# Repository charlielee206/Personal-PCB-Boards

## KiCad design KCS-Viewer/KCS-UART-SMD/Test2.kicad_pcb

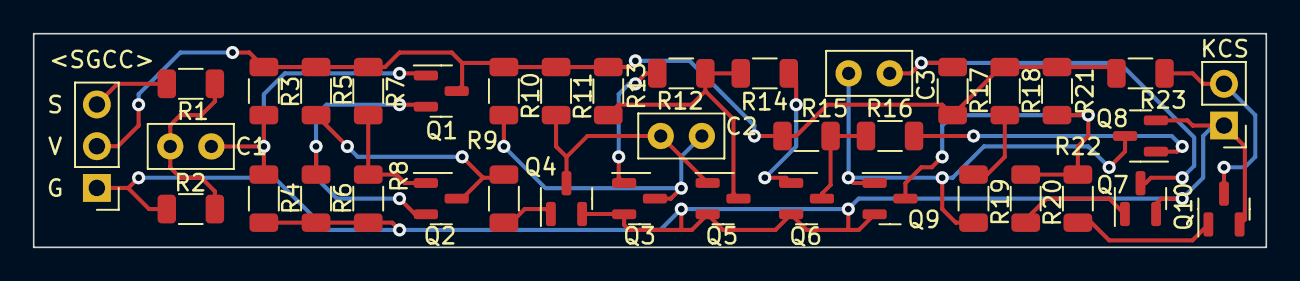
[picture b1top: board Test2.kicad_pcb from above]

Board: 2 copper layers, 75.0 x 13.0 mm, 38 parts (0 on the bottom side), 23 nets.

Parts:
C1, C2, C3: 100n; C_Disc_D5.0mm_W2.5mm_P2.50mm
G: Screw_Terminal_01x03; PinHeader_1x03_P2.54mm_Vertical
KCS: Screw_Terminal_01x02; PinHeader_1x02_P2.54mm_Vertical
Q1, Q2, Q3, Q4, Q5, Q6, Q7, Q8, Q9, Q10: MMBT3904; SOT-23
R1: 150R; R_1206_3216Metric
R2: 75R; R_1206_3216Metric
R3, R7, R9, R12, R14, R16, R20, R22: 10K; R_1206_3216Metric
R4, R8: 3K; R_1206_3216Metric
R5, R10, R13, R15, R17, R21, R23: 2R2K; R_1206_3216Metric
R6: 100R; R_1206_3216Metric
R11: 22K; R_1206_3216Metric
R18: 12K; R_1206_3216Metric
R19: 68K; R_1206_3216Metric

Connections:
GND: G.1, KCS.1, Q3.2 (E), Q4.2 (E), Q5.2 (E), Q6.2 (E), Q7.2 (E), Q8.2 (E), Q9.2 (E), Q10.2 (E), R2.2, R4.2, R6.2, R8.2
unnamed: C1.1, R1.2, R2.1
unnamed: KCS.2, Q10.3 (C), R23.2
unnamed: C1.2, Q1.1 (B), R3.2, R4.1
unnamed: Q1.2 (E), Q2.2 (E), R6.1
unnamed: G.3, R1.1
unnamed: Q2.3 (C), R5.2, R9.1
unnamed: G.2, Q1.3 (C), R3.1, R5.1, R7.1, R10.1, R11.1, R13.1, R15.1, R17.1, R18.1, R21.1, R23.1
unnamed: Q2.1 (B), R7.2, R8.1
unnamed: Q4.1 (B), R9.2
unnamed: C2.1, Q3.3 (C), R10.2
unnamed: C2.2, Q4.3 (C), Q5.1 (B), R11.2
unnamed: Q3.1 (B), R12.1
unnamed: Q5.3 (C), R12.2, R13.2, R14.1
unnamed: Q6.1 (B), R14.2
unnamed: Q6.3 (C), R15.2, R16.1
unnamed: Q8.1 (B), R16.2
unnamed: C3.1, Q7.3 (C), R17.2
unnamed: R18.2, R19.1
unnamed: C3.2, Q8.3 (C), Q9.1 (B), R19.2
unnamed: Q7.1 (B), R20.1
unnamed: Q9.3 (C), R20.2, R21.2, R22.1
unnamed: Q10.1 (B), R22.2

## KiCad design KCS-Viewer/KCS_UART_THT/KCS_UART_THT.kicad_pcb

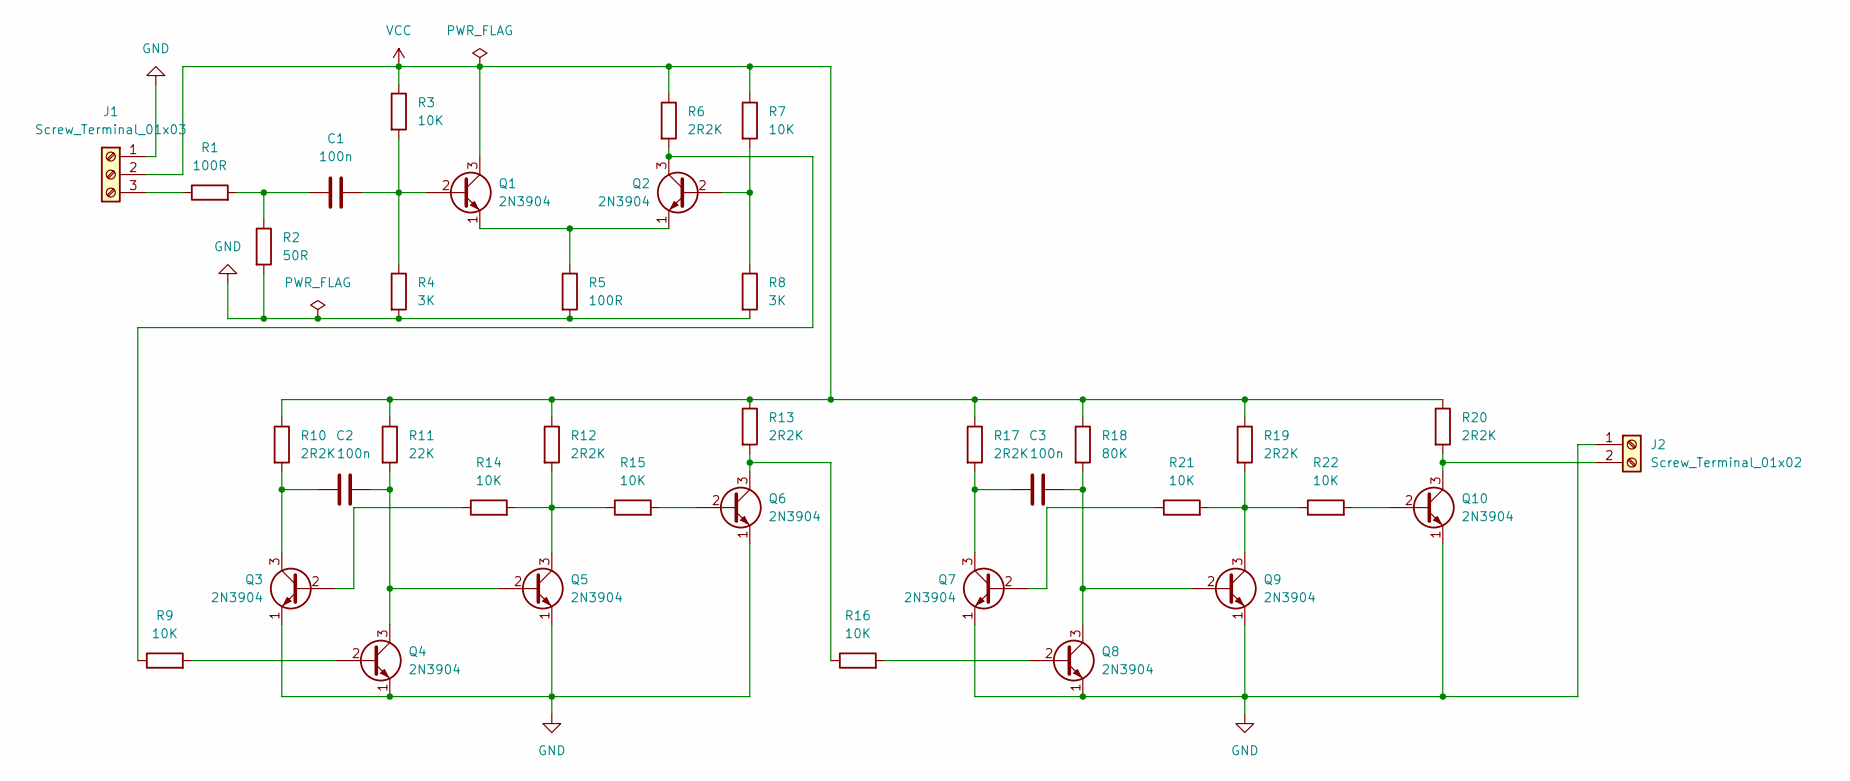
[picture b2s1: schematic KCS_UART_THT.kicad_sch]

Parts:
C1, C2, C3: 100n; C_Disc_D5.0mm_W2.5mm_P2.50mm
J1: Screw_Terminal_01x03; PinHeader_1x03_P2.54mm_Vertical
J2: Screw_Terminal_01x02; PinHeader_1x02_P2.54mm_Vertical
Q1, Q2, Q3, Q4, Q5, Q6, Q7, Q8, Q9, Q10: 2N3904; TO-92_Inline
R1, R5: 100R; R_Axial_DIN0207_L6.3mm_D2.5mm_P10.16mm_Horizontal
R2: 50R; R_Axial_DIN0207_L6.3mm_D2.5mm_P10.16mm_Horizontal
R3, R7, R9, R14, R15, R16, R21, R22: 10K; R_Axial_DIN0207_L6.3mm_D2.5mm_P10.16mm_Horizontal
R4, R8: 3K; R_Axial_DIN0207_L6.3mm_D2.5mm_P10.16mm_Horizontal
R6, R10, R12, R13, R17, R19, R20: 2R2K; R_Axial_DIN0207_L6.3mm_D2.5mm_P10.16mm_Horizontal
R11: 22K; R_Axial_DIN0207_L6.3mm_D2.5mm_P10.16mm_Horizontal
R18: 80K; R_Axial_DIN0207_L6.3mm_D2.5mm_P10.16mm_Horizontal

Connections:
GND: J1.1, J2.1, Q3.1 (E), Q4.1 (E), Q5.1 (E), Q6.1 (E), Q7.1 (E), Q8.1 (E), Q9.1 (E), Q10.1 (E), R2.2, R4.2, R5.2, R8.2; also elsewhere on the board
unnamed 1: J1.3, R1.1; also elsewhere on the board
unnamed: C1.1, R1.2, R2.1
unnamed: C1.2, Q1.2 (B), R3.2, R4.1
unnamed: Q1.1 (E), Q2.1 (E), R5.1
unnamed: Q2.3 (C), R6.2, R9.1
unnamed: Q2.2 (B), R7.2, R8.1
unnamed: Q4.2 (B), R9.2
unnamed: C2.1, Q3.3 (C), R10.2
unnamed: C2.2, Q4.3 (C), Q5.2 (B), R11.2
unnamed: Q5.3 (C), R12.2, R14.2, R15.1
unnamed: Q6.3 (C), R13.2, R16.1
unnamed: Q3.2 (B), R14.1
unnamed: Q6.2 (B), R15.2
unnamed: Q8.2 (B), R16.2
unnamed: C3.1, Q7.3 (C), R17.2
unnamed: C3.2, Q8.3 (C), Q9.2 (B), R18.2
unnamed: Q9.3 (C), R19.2, R21.2, R22.1
unnamed 18: J2.2, Q10.3 (C), R20.2; also elsewhere on the board
unnamed: Q7.2 (B), R21.1
unnamed: Q10.2 (B), R22.2
VCC: J1.2, Q1.3 (C), R3.1, R6.1, R7.1, R10.1, R11.1, R12.1, R13.1, R17.1, R18.1, R19.1, R20.1; also elsewhere on the board

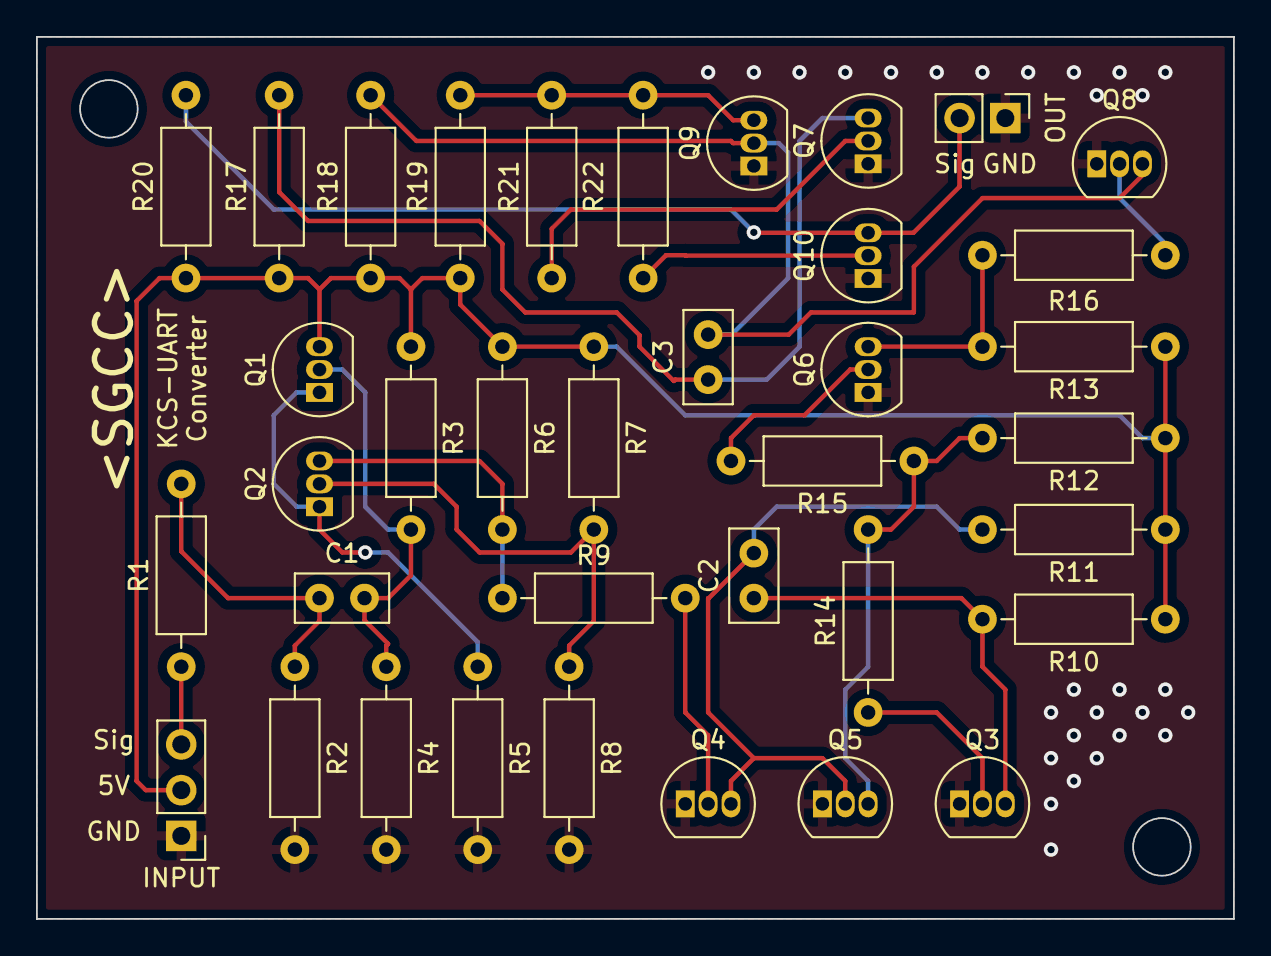
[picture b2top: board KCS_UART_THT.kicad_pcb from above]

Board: 2 copper layers, 66.5 x 49.0 mm, 37 parts (0 on the bottom side), 22 nets.

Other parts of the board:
INPUT: Screw_Terminal_01x03; PinHeader_1x03_P2.54mm_Vertical
OUT: Screw_Terminal_01x02; PinHeader_1x02_P2.54mm_Vertical

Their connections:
GND: INPUT.1, OUT.1; also elsewhere on the board
unnamed 1: INPUT.3; also elsewhere on the board
unnamed 18: OUT.2; also elsewhere on the board
VCC: INPUT.2; also elsewhere on the board
